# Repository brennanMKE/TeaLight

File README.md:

# TeaLight

A rechargeable, IR-controlled flameless tea light built around an ATtiny85. Home Assistant owns the schedule and sends NEC IR commands through an ESPHome IR blaster; each light only receives commands, flickers its LEDs, and manages its LiPo battery.

The full design spec is in [tea-light-design.md](tea-light-design.md).

## Hardware at a glance

| Block | Part | Notes |
|---|---|---|
| MCU | ATtiny85-20SU (SOIC-8) | Internal 8 MHz, runs directly from VBAT, no regulator |
| Charger | MCP73831T-2ACI/OT | 4.2 V, ~100 mA (R_PROG = 10 kΩ), STAT → PB3 |
| Power in | USB-C (power-only) + optional pogo tray pads | 5.1 kΩ CC pull-downs; BAT54 on the tray input |
| Battery | 1S LiPo, 100–200 mAh, with protection PCM | Optional slide switch for shipping |
| IR receiver | Vishay TSOP75238TT (38 kHz, top view) | 100 Ω / 4.7 µF supply filter, OUT → PB2 (INT0) |
| LEDs | 2 × warm white / amber, 150 Ω each | PWM on OC0A (PB0) and OC0B (PB1) |
| Programming | 6 ISP pads on the bottom | Pogo-pin jig or Tag-Connect TC2030 |

Target size: 32 mm round 2-layer PCB, 1.0 mm FR4, to fit a standard ~38 mm tea light shell.

## How it works

```
Home Assistant (sunset trigger, off after 6 h)
  -> ESPHome on ESP32-C3 + IR LED (NEC, address 0x5A)
    -> IR broadcast to the room
      -> each tea light: TSOP75238 -> ATtiny85 -> LEDs
```

NEC address `0x5A`:

| Command | Action |
|---|---|
| `0x01` | On |
| `0x02` | Off |
| `0x03` / `0x04` | Brightness up / down |
| `0x05` | Toggle flicker / steady |
| `0x06` | On with a local 6 h timer |
| `0x10`–`0x1F` | Group on |
| `0x20`–`0x2F` | Group off |

A learn mode (triggered on USB unplug) lets any spare NEC remote be paired as alternate On/Off codes.

## Repository layout

| Path | Contents | Status |
|---|---|---|
| `tea-light-design.md` | Design spec | Done |
| `docs/schematic.svg` | Circuit overview drawing | Done |
| `tea-light/` | KiCad 10 project: schematic, 32 mm PCB, project libraries, build scripts | Done (rev 0.1, unverified) |
| `tea-light/production/` | Gerber zip, JLCPCB BOM and CPL, 3D renders | Generated |
| `firmware/` | PlatformIO project for the ATtiny85 (ATTinyCore) | Planned |
| `ir-blaster.yaml` | ESPHome config for the IR blaster, plus HA automations | Planned |

## PCB

The board is generated from the schematic by scripts that use KiCad's bundled Python:

```sh
cd tea-light
/Applications/KiCad/KiCad.app/Contents/Frameworks/Python.framework/Versions/3.9/bin/python3 scripts/build_board.py
scripts/export_fab.sh   # ERC, DRC, Gerber zip, JLCPCB BOM/CPL, renders
```

`build_board.py` places parts, routes with a small built-in maze router (`routes.py`), and pours GND on both layers. Re-running it overwrites manual edits to the PCB.

Before ordering:

- J1 (GCT USB4125-GF-A) and D1/D2 (0603 warm white) have no LCSC part yet, and U2 and U3 showed no JLCPCB stock when mapped. Source or substitute them.
- Check the TSOP75238TT footprint against the Vishay drawing, and check the CPL rotations in JLCPCB's preview.
- Parts are on both sides, which JLCPCB charges extra to assemble.

## Roadmap

1. Firmware: state machine, flicker, VCC measurement, command set, learn mode
2. ESPHome IR blaster config and Home Assistant automations
3. Bring-up checklist: fuses, IR decode, current measurements, range through the shell

## Open questions

- Interior dimensions of the shell, and whether its diffuser passes 940 nm IR
- One LED or two
- USB-C per unit, a charging tray, or both
- Whether TSOP standby current justifies duty-cycling its supply

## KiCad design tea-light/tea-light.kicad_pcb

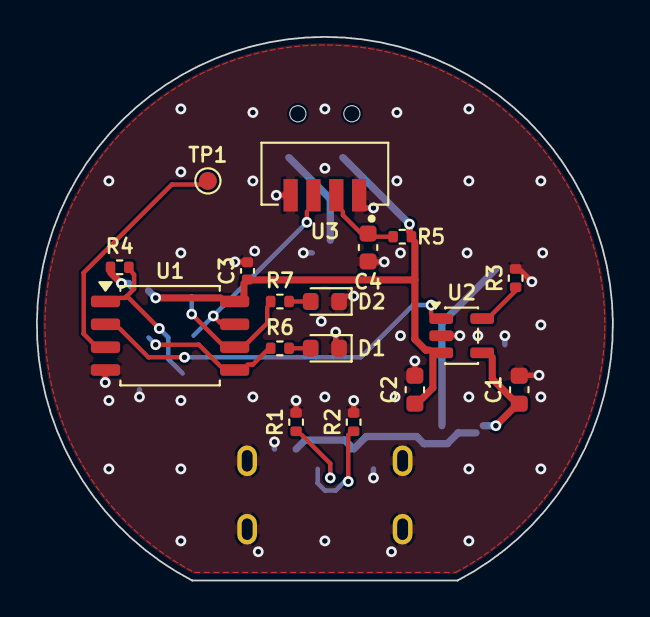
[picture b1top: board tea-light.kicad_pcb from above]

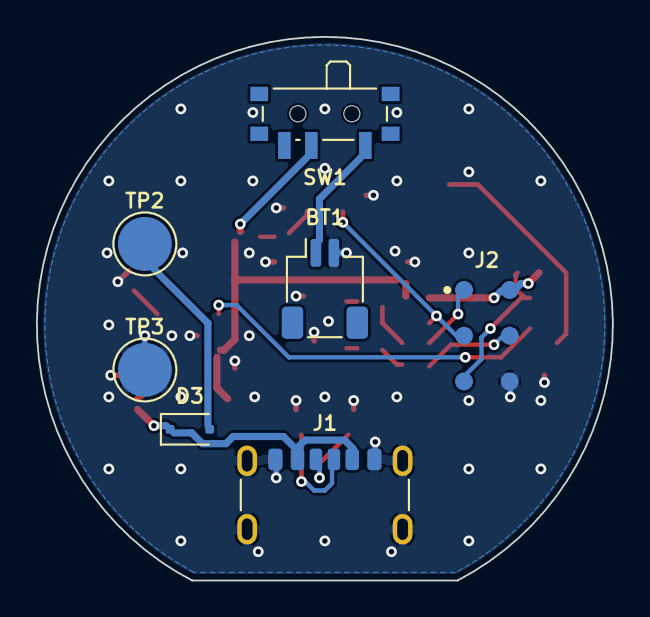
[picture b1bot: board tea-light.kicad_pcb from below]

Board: 2 copper layers, 32.0 x 30.2 mm, 24 parts (7 on the bottom side), 17 nets.

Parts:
BT1: LiPo 1S 150mAh w/ PCM; JST_SH_SM02B-SRSS-TB_1x02-1MP_P1.00mm_Horizontal
C1, C2, C4: 4.7u; C_0603_1608Metric
C3: 100n; C_0402_1005Metric
D1, D2: LED warm white; LED_0603_1608Metric
D3: BAT54J; D_SOD-323F
J1: USB-C PWR 6P; USB_C_Receptacle_GCT_USB4125-xx-x_6P_TopMnt_Horizontal
J2: ISP; ISP_Pogo_2x03_P2.54mm_Pad1.0mm
R1, R2: 5.1k; R_0402_1005Metric
R3, R4: 10k; R_0402_1005Metric
R5: 100; R_0402_1005Metric
R6, R7: 150; R_0402_1005Metric
SW1: SW_SPDT; SW_SPDT_PCM12
TP1: PB4_SPARE; TestPoint_Pad_D1.0mm
TP2: TRAY_VBUS; TestPoint_Pad_D3.0mm
TP3: TRAY_GND; TestPoint_Pad_D3.0mm
U1: ATtiny85-20SU; SOIC-8_5.3x5.3mm_P1.27mm
U2: MCP73831T-2ACI/OT; SOT-23-5
U3: TSOP75238TT; Vishay_Heimdall_TSOP752xx_TT_TopView

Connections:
BAT_P: BT1.1, SW1.1
CC1: J1.A5, R1.1
CC2: J1.B5, R2.1
GND: BT1.2, C1.2, C2.2, C3.2, C4.2, D1.1, D2.1, J1.A12, J1.B12, J1.SH, J2.6, R1.2, R2.2, R3.2, TP3.1, U1.4, U2.2, U3.1, U3.4
IR_OUT: J2.3, U1.7, U3.3
IR_VS: C4.1, R5.2, U3.2
LED1: J2.4, R6.1, U1.5
LED1_A: D1.2, R6.2
LED2: J2.1, R7.1, U1.6
LED2_A: D2.2, R7.2
PROG: R3.1, U2.5
RESET: J2.5, R4.2, U1.1
SPARE: TP1.1, U1.3
STAT: U1.2, U2.1
TRAY_VBUS: D3.2, TP2.1
VBAT: C2.1, C3.1, J2.2, R4.1, R5.1, SW1.2, U1.8, U2.3
VBUS: C1.1, D3.1, J1.A9, J1.B9, U2.4

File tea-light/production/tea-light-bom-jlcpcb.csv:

"Comment","Designator","Footprint","LCSC Part #"
"LiPo 1S 150mAh w/ PCM","BT1","Connector_JST:JST_SH_SM02B-SRSS-TB_1x02-1MP_P1.00mm_Horizontal","C160402"
"4.7u","C1,C2,C4","Capacitor_SMD:C_0603_1608Metric","C19666"
"100n","C3","Capacitor_SMD:C_0402_1005Metric","C1525"
"LED warm white","D1,D2","LED_SMD:LED_0603_1608Metric",""
"BAT54J","D3","Diode_SMD:D_SOD-323F","C130415"
"USB-C PWR 6P","J1","Connector_USB:USB_C_Receptacle_GCT_USB4125-xx-x_6P_TopMnt_Horizontal",""
"5.1k","R1,R2","Resistor_SMD:R_0402_1005Metric","C25905"
"10k","R3,R4","Resistor_SMD:R_0402_1005Metric","C25744"
"100","R5","Resistor_SMD:R_0402_1005Metric","C25076"
"150","R6,R7","Resistor_SMD:R_0402_1005Metric","C25082"
"SW_SPDT","SW1","Button_Switch_SMD:SW_SPDT_PCM12","C221841"
"ATtiny85-20SU","U1","Package_SO:SOIC-8_5.3x5.3mm_P1.27mm","C31540447"
"MCP73831T-2ACI/OT","U2","Package_TO_SOT_SMD:SOT-23-5","C424093"
"TSOP75238TT","U3","tea-light:Vishay_Heimdall_TSOP752xx_TT_TopView","C5248434"
